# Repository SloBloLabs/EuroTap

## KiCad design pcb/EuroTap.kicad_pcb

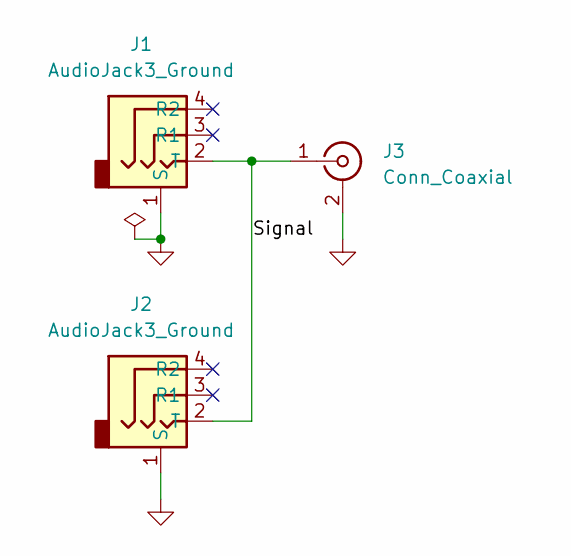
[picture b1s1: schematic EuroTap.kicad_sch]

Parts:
J1, J2: AudioJack3_Ground; Jack_3.5mm_PJ311_Horizontal
J3: Conn_Coaxial; SMA_Samtec_SMA-J-P-X-ST-EM1_EdgeMount

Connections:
/Signal: J1.2 (T), J2.2 (T), J3.1 (In)
GND: J1.1 (S), J2.1 (S), J3.2 (Ext)

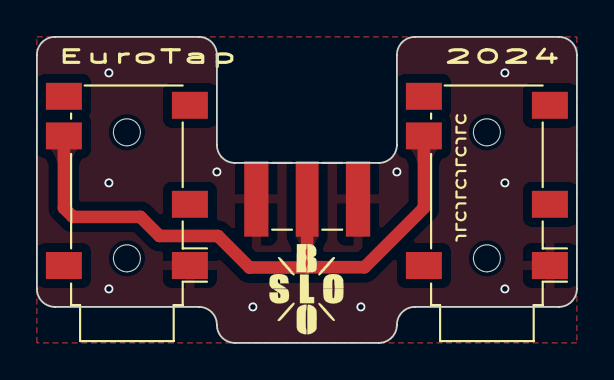
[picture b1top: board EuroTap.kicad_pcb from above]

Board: 2 copper layers, 30.0 x 17.0 mm, 4 parts (0 on the bottom side), 2 nets.

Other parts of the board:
Ref**: Val**; SloBloLogo

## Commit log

2024-02-25 initial upload
2024-02-26 KiCad 8.0
2024-03-01 Add teardrops
2024-03-03 30cm width
